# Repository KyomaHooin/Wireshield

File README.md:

DESCRIPTION

Server Rack Waste Heat Monitoring.

FILE
<pre>
                 avr/ - Atmega code.
               photo/ - Photo documentation.
               kicad/ - KiCAD schematic and PCB.
            openscad/ - OpenSCAD case model.
           raspberry/ - RPi code.
wireshield_schema.pdf - Shield schematic.
</pre>
SOURCE

https://github.com/KyomaHooin/Wireshield

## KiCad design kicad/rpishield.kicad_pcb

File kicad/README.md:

DESCRIPTION

Raspberry RPi2 OneWire AVR shield PCB.

FILE
<pre>
                3d/ - 3D models by Walter Lain (c) 2015.
  footprint.pretty/ - Custom footprints.
rpishield.kicad_pcb - PCB layout.
      rpishield.pro - Project file.
      rpishield.lib - Project library.
      rpishield.sch - Custom schematic.
      rpishield.net - Trace list.
  shield_screen.png - Board screenshot.
</pre>
SOURCE

https://github.com/KyomaHooin/Wireshield

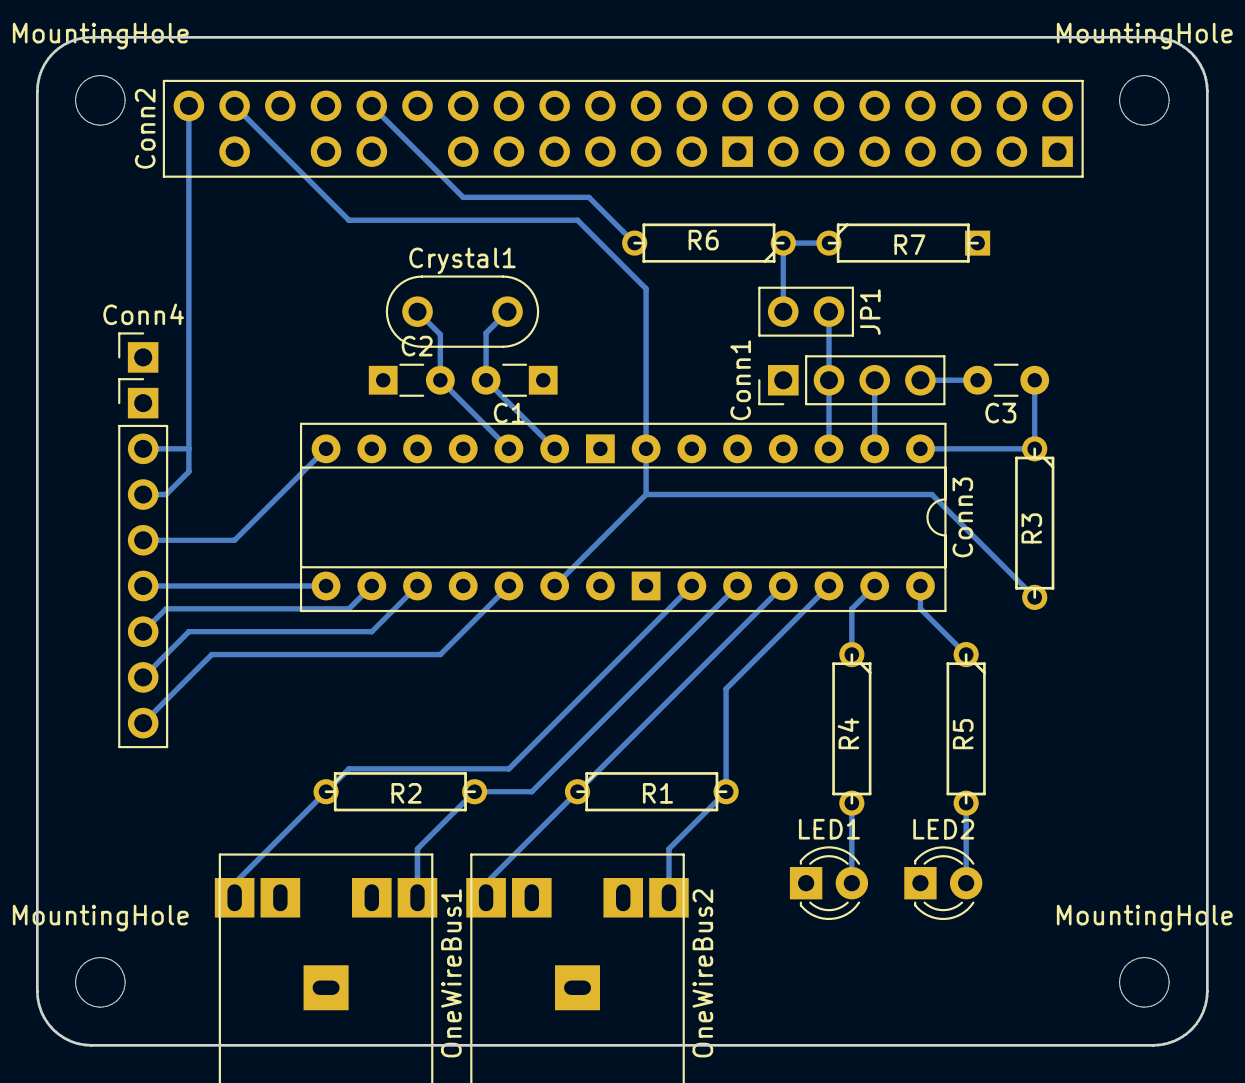
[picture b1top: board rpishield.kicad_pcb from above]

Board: 2 copper layers, 65.0 x 56.0 mm, 24 parts (0 on the bottom side), 24 nets.

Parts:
C1, C2: 22pF; Custom_Disc_D3.0mm_W1.6mm_P3.175mm
C3: 100nF; Custom_Disc_D3.0mm_W1.6mm_P3.175mm_normal
Conn1: UART; Socket_Strip_Straight_1x04_Pitch2.54mm
Conn2: RPi; Custom_Header_2x20_Pitch2.54mm
Conn3: Atmega328; Custom_DIP-28_W7.62mm_Socket
Conn4: SPI; Custom_Pin_Header_Straight_1x09_Pitch2.54mm
Crystal1: 16Mhz; Resonator-2pin_w8.0mm_h3.5mm
JP1: Jumper; Custom_Pin_Header_Straight_1x02_Pitch2.54mm
LED1, LED2: 10mA 2V; LED_D3.0mm_FlatTop
MountingHole: MountingHole_2.75mm_M2.5; Custom_MountingHole_2.75mm_M2.5
MountingHole#2, MountingHole#3, MountingHole#4: MountingHole_2.75mm_M2.5; Custom_MountingHole_2.75mm_M2.5
OneWireBus1, OneWireBus2: JACK_4P; Custom_Barrel_Jack
R1, R2: 4k7; Custom_R3_normal
R3, R6: 10k; Custom_R3_normal
R4, R5: 330; Custom_R3_normal
R7: 20k; Custom_R3

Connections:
/BUS1_DQ: Conn3.24, OneWireBus1.2, R2.2
/BUS1_PWR: Conn3.23, OneWireBus1.5, R2.1
/BUS2_DQ: Conn3.26, OneWireBus2.2, R1.2
/BUS2_PWR: Conn3.25, OneWireBus2.5, R1.1
/LED_ACC: Conn3.27, R4.1
/LED_PWR: Conn3.28, R5.1
/RST: C3.1, Conn3.1, R3.1
/RX: Conn1.3, Conn3.2
/RX_RPI: Conn2.10, R6.2
/SPI_MOSI: Conn3.17, Conn4.8
/SPI_SCK: Conn3.19, Conn4.9
/SPI_SS: Conn3.16, Conn4.7
/TFT_DC: Conn3.14, Conn4.5
/TFT_RST: Conn3.15, Conn4.6
/TX: Conn1.2, Conn3.3, JP1.1
/VCC_ADC: Conn2.4, Conn3.7, Conn3.20, R3.2
/VCC_LED: Conn2.2, Conn4.3, Conn4.4
/XTAL1: C1.2, Conn3.9, Crystal1.2
/XTAL2: C2.2, Conn3.10, Crystal1.1
GND: C1.1, C2.1, Conn1.1, Conn2.25, Conn2.39, Conn3.8, Conn3.22, Conn4.1, Conn4.2, LED1.1, LED2.1, OneWireBus1.1, OneWireBus2.1, R7.2
unnamed: C3.2, Conn1.4
unnamed: JP1.2, R6.1, R7.1
unnamed: LED1.2, R4.2
unnamed: LED2.2, R5.2

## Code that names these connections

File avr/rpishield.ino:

//
// RPi OneWire Shield 
//

#include<OneWire.h>
#include<LowPower.h>
#include<TFT_22_ILI9225.h>// 176x220

#define BUS1_PWR A0
#define BUS1_DQ  A1
#define BUS2_PWR A2
#define BUS2_DQ  A3
#define LED_ACC  A4
#define LED_PWR  A5
#define TFT_RS   8 // TFT D/C
#define TFT_RST  9 // TFT RST
#define TFT_CS   10// SPI SS
#define TFT_SDI  11// SPI MOSI
#define TFT_CLK  13// SPI SCK

//OneWire instance
OneWire Bus1(BUS1_DQ);
OneWire Bus2(BUS2_DQ);
//TFT HW SPI instance
TFT_22_ILI9225 tft(TFT_RST,TFT_RS,TFT_CS,0);

//VAR

int maxtemp = 30;// Maximum temperature.

byte sensor[8][8] = {
  0x28,0xff,0xaa,0xd9,0xb2,0x17,0x04,0x44,// Bus1[sensor 1-4]
  0x28,0xff,0x98,0x07,0xb2,0x17,0x04,0x57,
  0x28,0xff,0xa5,0x2b,0xb2,0x17,0x05,0x03,
  0x28,0xff,0x4c,0xd6,0xb1,0x17,0x04,0x7c,
  0x28,0xff,0x7b,0xb2,0xb1,0x17,0x04,0x37,// Bus2[sensor 5-8]
  0x28,0xff,0x8f,0x96,0xb1,0x17,0x04,0xf0,
  0x28,0xff,0x25,0xb1,0xb1,0x17,0x04,0x88,
  0x28,0xff,0x1b,0xb0,0x70,0x16,0x05,0x43
};

//SETUP

void setup() {
  //UART
  Serial.begin(9600);
  //OneWire
  pinMode(BUS1_PWR, OUTPUT);
  digitalWrite(BUS1_PWR, HIGH);
  pinMode(BUS2_PWR, OUTPUT);
  digitalWrite(BUS2_PWR, HIGH);
  //LED
  pinMode(LED_PWR, OUTPUT);
  digitalWrite(LED_PWR, HIGH);
  pinMode(LED_ACC, OUTPUT);
  digitalWrite(LED_ACC, LOW); 
  //TFT
  tft.begin();
  tft.setOrientation(1);
  tft.setFont(Terminal6x8);
  tft.clear();
}

//MAIN

void loop() {
  float temperature;
  char msg[6], payload[48] = {};
  for (int i = 0; i < 4; i++) {
    ds_temp_request(Bus1,sensor[i]);
    temperature = ds_get_temperature(Bus1,sensor[i]);
    if ( temperature <= 0 ) { temperature = 0; }
    sprintf(msg, "S%dT%03d", i, int(temperature * 10));
    strcat(payload,msg);
    tft_update(i,temperature);
  }
  for (int i = 4; i < 8; i++) {
    ds_temp_request(Bus2,sensor[i]);
    temperature = ds_get_temperature(Bus2,sensor[i]);
    if ( temperature <= 0 ) { temperature = 0; }
    sprintf(msg, "S%dT%03d", i, int(temperature * 10));
    strcat(payload,msg);
    tft_update(i,temperature);
  }
  Serial.println(payload);
  led_flash();
  for (int i = 0; i < 74; i++) {// 5min sleep
    LowPower.powerDown(SLEEP_4S, ADC_OFF, BOD_OFF);
  }
}

//FUNC

//Blink half a sec.
void led_flash() {
  digitalWrite(LED_ACC,HIGH);
  delay(100);
  digitalWrite(LED_ACC,LOW);
}

//Bus request temperature
void ds_temp_request(OneWire &ds, byte addr[8]) {
  ds.reset();
  ds.select(addr);
  ds.write(0x44);//"Convert T".
  delay(750); //12-Bit resolution delay.
}

//Bus calculate temperature.
float ds_get_temperature(OneWire &ds, byte addr[8]) {
  byte ds_data[2];
  ds.reset();
  ds.select(addr);
  ds.write(0xbe); //"Read Scratchpad".
  ds.read_bytes(ds_data,2); //LSB & MSB
  short raw = ds_data[1] << 8 | ds_data[0]; //2-Byte to 16 bit int
  return (float)raw / 16.0; //-> int to double precission float
}

//TFT background template 52x85 square 2px spacing
void tft_rectangle(int id, float val) {
  unsigned long color;
  (val > 0 && val < maxtemp) ? color = COLOR_GREEN : color = COLOR_RED;
  if(id < 4) {
     tft.drawRectangle(2 + 2*id + 52*id, 2, 54 + 2*id + 52*id, 87, color);
     tft.drawRectangle(2 + 2*id + 52*id + 1, 3, 54 + 2*id + 52*id - 1, 86, color);
  } else {
     tft.drawRectangle(2 + 2*(id-4) + 52*(id-4), 89, 54 + 2*(id-4) + 52*(id-4), 174 , color);
     tft.drawRectangle(2 + 2*(id-4) + 52*(id-4) + 1, 90, 54 + 2*(id-4) + 52*(id-4) - 1, 173 , color);
  }
}

//TFT draw value
void tft_update(int id, float val) {
  String offset;
  String sid = String("R") + String(id + 1);
  if (val >= 0 && val < 10) { offset = String(' '); }
  String tmp = offset + String(int(val)) + String(".") + String(int(val*10) % 10);
  if (id < 4) {
      tft.drawText(21 + 2*id + 52*id, 28, sid, COLOR_WHITE);
      tft.drawText(15 + 2*id + 52*id, 53, tmp, COLOR_WHITE);
  } else {
      tft.drawText(21 + 2*(id-4) + 52*(id-4), 115, sid, COLOR_WHITE);
      tft.drawText(15 + 2*(id-4) + 52*(id-4), 140, tmp, COLOR_WHITE);
  }
  tft_rectangle(id, val);
}

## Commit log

2017-02-21 Init README.
2017-02-21 Kicad schema.
2017-02-21 Schema update.
2017-02-21 Fix conn label.
2017-02-22 Kicad schema, PCB update.
2017-02-22 Schema PDF update.
2017-02-23 PCB schematic update.
2017-02-23 3D models.
2017-02-23 Project screen.
2017-02-23 Fix readme URL.
2017-02-23 Move schematic PDF to homepage.
2017-02-24 Round corner, via, gnd pour.
2017-02-25 20x2 pin strip.
2017-02-25 Obsolate footprint.
2017-02-25 Distance rule, custom header.
2017-02-25 Ground fill, RPi pinhole, schema lib, cleanup.
2017-02-25 Typo.
2017-02-25 Simplifiled structure.
2017-02-26 Obsolate models, RX/RT fix.
2017-02-26 Ground pad, track cleanup.
2017-02-26 Update schema lib.
2017-02-26 Better Jack track.
2017-02-27 TODO.
2017-02-27 Todo update.
2017-03-01 More todo.
2017-03-01 LCD spec.
2017-03-01 IDC spec.
2017-03-03 Readme update.
2017-03-16 Custom footprint library.
2017-03-16 SPI, LED, R, C footprint, path update.
2017-03-16 Kicad models, obsolate.
2017-03-16 Screen update.
2017-03-19 DODO update.
2017-03-20 Scad init.
2017-03-21 AVR Demo.
2017-03-22 Minor fix, typo.
2017-03-22 Revert test.
2017-03-23 Minor typo.
2017-03-23 Reamde.
2017-03-24 Refresh, sleep, cleanup.
2017-03-25 SCAD TODO.
2017-03-30 TFT SPI, schema update.
2017-04-03 RPi init.
2017-04-03 More simple.
2017-04-04 Case code update.
2017-04-04 Top, bottom update.
2017-04-04 Case model screen.
2017-04-04 Kicad cleanup.
2017-04-04 Update.
2017-04-05 Mount hole/buffer.
2017-04-06 Firewall.
2017-04-06 Config update.
2017-04-06 Dir rename.
2017-04-06 Struct update.
2017-04-06 Console config.
2017-04-06 Pi,shield components.
2017-04-06 SPI, spacer.
2017-04-07 Fix xonxoff flow control.
2017-04-07 Eth0 config.
2017-04-07 Stdout newline.
2017-04-07 Top case, raw shiled component.
2017-04-07 Install update.
2017-04-08 RRD.
2017-04-08 Frontend.
2017-04-08 WWW config.
2017-04-08 Email notify.
2017-04-09 Payload concat.
2017-04-09 AVR delay, var fix.
2017-04-10 Input parsing.
2017-04-11 RRD template.
2017-04-11 RRD update, plot.
2017-04-12 OneWire PWR fix.
2017-04-12 Sensor var, payload fix.
2017-04-12 Temperature error.
2017-04-12 Heatbeat tune.
2017-04-12 Logic update.
2017-04-12 rc.local, TODO.
2017-04-12 HTTP/S.
2017-04-12 Linebreak.
2017-04-12 File update.
2017-04-13 Better logging.
2017-04-13 Lower temperature fix.
2017-04-13 Obsolate module.
2017-04-13 General update exception.
2017-04-15 String fixes.
2017-04-15 Repack.
2017-04-15 Syntax, printing, TFT default.
2017-04-15 Patch UL color, for loop.
2017-04-15 TFT init, fc update.
2017-04-17 Stereo 4P jack foot.
2017-04-17 Stereo jack schema.
2017-04-17 Stereo jack update.
2017-04-17 Sqare matrix.
2017-04-17 SPI foot.
2017-04-18 TFT screen.
2017-04-18 More TFT code.
2017-04-18 Better sprintf.
2017-04-19 Orientation, buffer, spritf, ID,String.
2017-04-20 Mounthole,Jack,Crystal PCB fix.
2017-04-20 Board,LED,AVR spacing.
2017-04-20 Hole fix.
2017-04-20 Screen update 2.
2017-04-22 Crystal layout.
2017-04-22 Jack oval width.
2017-04-22 Jack update.
2017-04-22 Jack 3D model fix.
2017-04-24 Valid ROM, TFT offset tune.
2017-04-26 Syntax typo.
2017-04-27 Last, averare RRA.
2017-04-27 Serial debug.
2017-04-27 Graph interval label.
2017-04-27 Graph output formating.
2017-04-27 Plot screen.
2017-04-27 Serial config.
2017-04-27 5 min delay.
2017-04-28 Frontend nice.
2017-04-28 LowPower lib.
2017-04-28 Idle, LED blink.
2017-04-28 Plot formating.
2017-04-28 Offset fix.
2017-05-02 Idle/sleep, acct. lex fix.
2017-05-10 TFT dimmensions.
2017-05-11 Revert formating.
2017-07-18 Create Photo
2017-07-18 Create photodocumentation
2017-07-18 Update photodocumentation
2017-07-18 Typo, readme update.
2017-07-20 Fix PDF export.
2017-07-20 RST path.
2017-07-20 Jack schema, RST bug.
2017-07-20 Rule check.
2017-08-02 Disable serial TTY service.
2017-08-03 Contrast colors, alignment.
2017-08-07 Header, MOSI, RX, Jumper update.
2017-08-07 Jumper.
2017-08-07 Header, MOSI, RX, Jumper.
2017-08-07 RPI header,Jumper.
2017-08-07 SPI VCC, Jumper, MOSI track.
2017-08-07 SPI/AVR VCC, TX drop.
2017-08-07 0.3mm track.
2017-08-07 Un-debug.
2017-08-09 Switch RS/RST.
2017-08-10 R/C footprint update.
2017-08-10 R/C footprint pad + 0.625 mm.
2017-08-10 Layout tune, 3D offsets.
2017-08-10 Layout update.
2017-08-10 LED R offset fix.
2017-08-11 Obsolate.
2017-08-17 Dimension schematics.
2017-08-17 RPi dimensions.
2017-08-18 Code update.
2017-08-18 TFT code.
2017-08-18 Shield code.
2017-08-18 RPi code.
2017-08-18 SPI, typo.
2017-08-18 New base rewrite backup.
2017-08-18 Order list.
2017-08-19 Support funtions.
2017-08-19 Func. name.
2017-08-19 Func. name, minor fixes.
2017-08-19 Rewritten code.
2017-08-21 Top/bottom height, liplock, vent.
2017-08-21 LED cylinder.
2017-08-22 Micro SD.
2017-08-22 IDC cable, MicroSD card, Vent loop.
2017-08-22 IDC schema.
2017-08-22 Dongle order.
2017-08-23 Top TFT hole.
2017-08-23 Display mount.
2017-08-23 Fix top display mount.
2017-08-24 Top display mount fix.
2017-08-26 Syntax.
2017-08-26 Display mount sink.
2017-08-27 Case mount hole.
2017-08-28 Plot screen update.
2017-08-30 Numeric update.
2017-08-31 Order update.
2017-08-31 Oder update.
2017-08-31 Minor fixes.
2017-09-04 Case rewrite.
2017-09-04 Dimensions update.
2017-09-07 Numeric update, code rewrite.
2017-09-07 RPi lip, SD cut, cleanup.
2017-09-07 SCAD screen update.
2017-09-07 Lip tune, grammar.
2017-09-07 Order update 2.
2017-09-07 Thickness tune.
2017-09-08 Lock, harden, fixes.
2017-09-08 Top / mount height fix.
2017-09-08 Bossard insert.
2017-09-08 Box screen update.
2017-09-08 Cleanup.
2017-09-09 Rounded PCB.
2017-09-09 Lip-lock fix.
2017-09-09 Show spacer, alignment.
2017-09-09 STL output.
2017-09-09 Reamde update.
2017-09-09 Syntax cleanup.
2017-09-09 Display screw update.
2017-09-09 Revert.
2017-09-10 Display screw update, display mount harden.
2017-09-11 USB,DHMI,IDC,LED,screen numeric update.
2017-09-14 Max temperature var.
2017-09-14 M2 insert spec.
2017-09-29 Regexp tune.
2017-10-16 Components update.
2017-10-25 RST/PWR button code.
2017-10-25 Webcam.
2017-10-25 Func. return.
2017-10-25 Update logic.
2017-10-25 Def name.
2017-10-26 Better logic.
2017-10-26 Button schema.
2017-10-26 Button model.
2017-10-26 Pwr/rst button.
2017-10-26 Button update.
2017-10-26 M7 buffer.
2017-11-18 Pin description.
2017-12-11 Fix lib name.
2017-12-11 Live code.
2018-01-02 Fix too short press.
2018-02-12 Sensor array descr.
2018-02-12 Maxtemp var, hex typo.
2018-02-12 HTML 5 min refresh.
2018-02-14 3D print.
2018-02-16 MicroUsb,HDMI width/length mismatch fix.
2018-02-16 TFT screen width/length fix.
2018-02-16 Button dia +1.
2018-02-16 LED +1mm dia.
2018-02-16 Button +1mm dia + height.
2018-02-16 Unused variable.
2018-02-16 LED +0.5mm Dia, JACK +1mm Width, JACK +8mm ring.
2018-02-17 Button 00.5mm offset.
2018-02-17 All compoment +1mm width/height +0.5mm offset.
2018-02-17 All +1mm width/length/dia +0.5mm offset.
2018-02-18 Lip-lock fixes.
2018-02-18 Shiled front spacer/harden -0.5mm.
2018-02-18 Box width/length +0.5mm.
2018-02-21 TFT 0.5mm top/bottom.
2018-02-21 Bottom mount/hole +0.5mm dia.
2018-02-21 Button position tune.
2018-02-21 Brass insert mount hole.
2018-02-21 USB lip harden.
2018-02-21 Top +1mm height.
2018-02-21 STL update.
2018-02-21 Perm fix.
2018-02-21 STL update jack.
2018-02-21 Minor offset fix.
2018-02-21 Jack height fix.
2018-02-27 It's waste heat..
2018-02-27 Contact update.
2018-03-07 Update rpishield.ino
    sensors serial number update
2018-03-08 Sensor update.
2018-03-08 Fix error value.
2018-03-08 Fix logic.
2018-03-08 Typo bug fix.
2018-03-08 Minor update.
2018-03-28 Fix microHeight bug.
2018-03-31 STL top update.
2018-03-31 STL bottom update.
2018-04-03 Jack possition fix.
2018-04-03 Lip lock fix.
2018-04-03 Top mount fix.
2018-04-14 Sensor error comment.
2018-05-16 Fix quotation.
2018-05-20 Final box.
2018-05-31 Fix string/float concat.
2018-06-01 Nice notification sender.
2018-06-01 Notification variable.
2018-06-03 Handle SMTP exception.
